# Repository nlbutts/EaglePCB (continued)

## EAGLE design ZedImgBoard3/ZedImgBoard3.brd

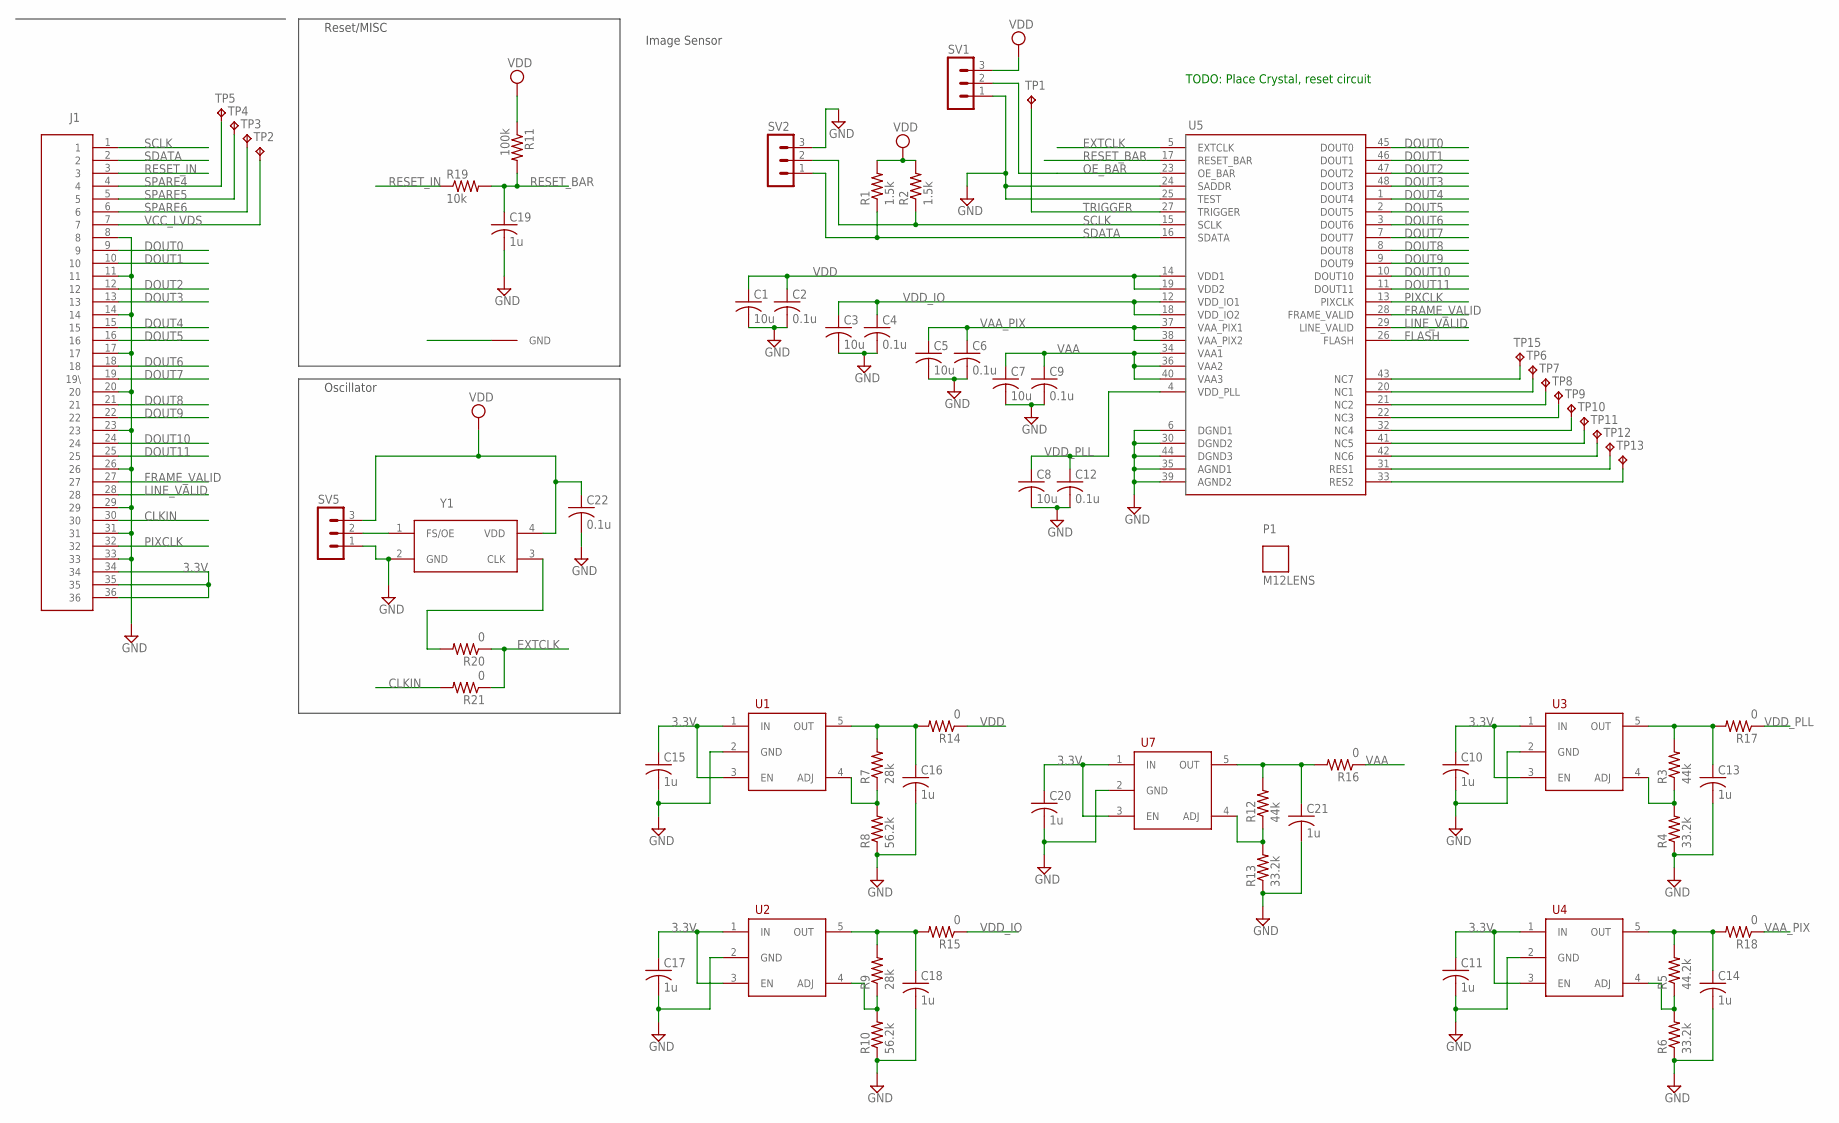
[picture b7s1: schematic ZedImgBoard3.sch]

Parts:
C1, C3, C5, C7, C8: 10u; C0805
C2, C4, C6, C9, C12, C22: 0.1u; C0805
C10, C11, C13, C14, C15, C16, C17, C18, C19, C20, C21: 1u; C0805
J1: MOLEX_54132_3662
P1: M12LENS
R1, R2: 1.5k; M0805
R3, R12: 44k; M0805
R4, R6, R13: 33.2k; M0805
R5: 44.2k; M0805
R7, R9: 28k; M0805
R8, R10: 56.2k; M0805
R11: 100k; M0805
R14, R15, R16, R17, R18, R20, R21: 0; M0805
R19: 10k; M0805
SV1, SV2, SV5: MA03-1
TP1, TP2, TP3, TP4, TP5, TP6, TP7, TP8, TP9, TP10, TP11, TP12, TP13, TP15: TPB1,27; B1,27
U1, U2, U3, U4, U7: TPS73201DB; SOT23-5
U5: AR0331; ILCC48
U$4: GND_LUG; GND_PAD
Y1: SILABS_501AAAXXD; 4-SMD

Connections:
1.8V: R1.2, R2.2
3.3V: C10.1, C11.1, C15.1, C17.1, C20.1, J1.34, J1.35, J1.36, U1.1 (IN), U1.3 (EN), U2.1 (IN), U2.3 (EN), U3.1 (IN), U3.3 (EN), U4.1 (IN), U4.3 (EN), U7.1 (IN), U7.3 (EN)
CLKIN: J1.30, R21.2
DOUT0: J1.9, U5.45 (DOUT0)
DOUT1: J1.10, U5.46 (DOUT1)
DOUT2: J1.12, U5.47 (DOUT2)
DOUT3: J1.13, U5.48 (DOUT3)
DOUT4: J1.15, U5.1 (DOUT4)
DOUT5: J1.16, U5.2 (DOUT5)
DOUT6: J1.18, U5.3 (DOUT6)
DOUT7: J1.19 (19\), U5.7 (DOUT7)
DOUT8: J1.21, U5.8 (DOUT8)
DOUT9: J1.22, U5.9 (DOUT9)
DOUT10: J1.24, U5.10 (DOUT10)
DOUT11: J1.25, U5.11 (DOUT11)
EXTCLK: R20.1, R21.1, U5.5 (EXTCLK)
FLASH: U5.26 (FLASH)
FRAME_VALID: J1.27, U5.28 (FRAME_VALID)
GND: C1.2, C2.2, C3.2, C4.2, C5.2, C6.2, C7.2, C8.2, C9.2, C10.2, C11.2, C12.2, C13.2, C14.2, C15.2, C16.2, C17.2, C18.2, C19.2, C20.2, C21.2, C22.2, J1.8, J1.11, J1.14, J1.17, J1.20, J1.23, J1.26, J1.29, J1.31, J1.33, R4.1, R6.1, R8.1, R10.1, R13.1, SV1.1, SV2.3, SV5.1, U1.2 (GND), U2.2 (GND), U3.2 (GND), U4.2 (GND), U5.6 (DGND1), U5.24 (SADDR), U5.25 (TEST), U5.30 (DGND2), U5.35 (AGND1), U5.39 (AGND2), U5.44 (DGND3), U7.2 (GND), U$4.P$1, Y1.2 (GND)
LINE_VALID: J1.28, U5.29 (LINE_VALID)
unnamed: R7.1, R8.2, U1.4 (ADJ)
unnamed: R9.1, R10.2, U2.4 (ADJ)
unnamed: R12.1, R13.2, U7.4 (ADJ)
unnamed: TP15.TP, U5.43 (NC7)
unnamed: TP6.TP, U5.20 (NC1)
unnamed: TP7.TP, U5.21 (NC2)
unnamed: TP8.TP, U5.22 (NC3)
unnamed: TP9.TP, U5.32 (NC4)
unnamed: TP10.TP, U5.41 (NC5)
unnamed: TP11.TP, U5.42 (NC6)
unnamed: TP12.TP, U5.31 (RES1)
unnamed: TP13.TP, U5.33 (RES2)
unnamed: SV5.2, Y1.1 (FS/OE)
unnamed: R20.2, Y1.3 (CLK)
unnamed: R3.1, R4.2, U3.4 (ADJ)
unnamed: R5.1, R6.2, U4.4 (ADJ)
OE_BAR: SV1.2, U5.23 (OE_BAR)
PIXCLK: J1.32, U5.13 (PIXCLK)
RESET_BAR: C19.1, R11.2, R19.2, U5.17 (RESET_BAR)
RESET_IN: J1.3, R19.1
SCLK: J1.1, R2.1, SV2.2, U5.15 (SCLK)
SDATA: J1.2, R1.1, SV2.1, U5.16 (SDATA)
SPARE4: J1.4, TP5.TP
SPARE5: J1.5, TP4.TP
SPARE6: J1.6, TP3.TP
TRIGGER: TP1.TP, U5.27 (TRIGGER)
VAA: C7.1, C9.1, R16.1, U5.34 (VAA1), U5.36 (VAA2), U5.40 (VAA3)
VAA_H: C21.1, R12.2, R16.2, U7.5 (OUT)
VAA_PIX: C5.1, C6.1, R18.1, U5.37 (VAA_PIX1), U5.38 (VAA_PIX2)
VAA_PIX_H: C14.1, R5.2, R18.2, U4.5 (OUT)
VCC_LVDS: J1.7, TP2.TP
VDD: C1.1, C2.1, C22.1, R11.1, R14.1, SV1.3, SV5.3, U5.14 (VDD1), U5.19 (VDD2), Y1.4 (VDD)
VDD_H: C16.1, R7.2, R14.2, U1.5 (OUT)
VDD_IO: C3.1, C4.1, R15.1, U5.12 (VDD_IO1), U5.18 (VDD_IO2)
VDD_IO_H: C18.1, R9.2, R15.2, U2.5 (OUT)
VDD_PLL: C8.1, C12.1, R17.1, U5.4 (VDD_PLL)
VDD_PLL_H: C13.1, R3.2, R17.2, U3.5 (OUT)

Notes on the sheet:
TODO: Place Crystal, reset circuit
Reset/MISC
Image Sensor
Oscillator

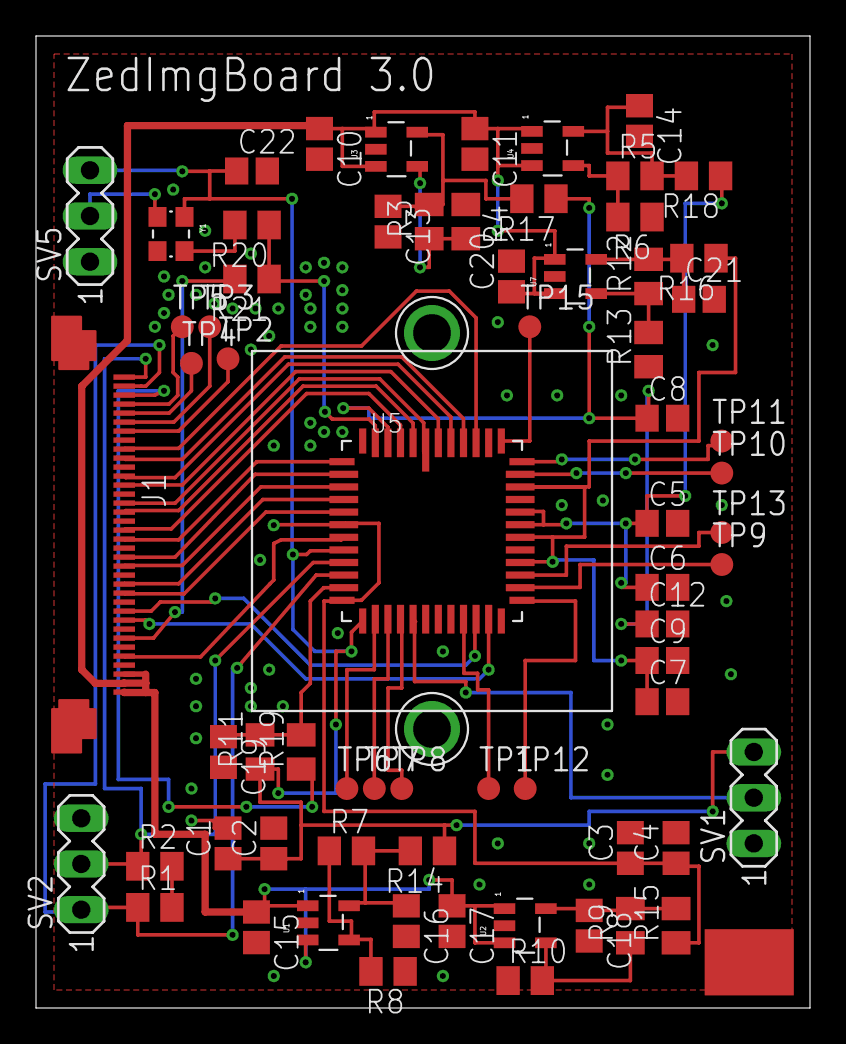
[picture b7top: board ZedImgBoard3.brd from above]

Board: 2 copper layers, 43.0 x 54.0 mm, 70 parts (0 on the bottom side), 56 nets.

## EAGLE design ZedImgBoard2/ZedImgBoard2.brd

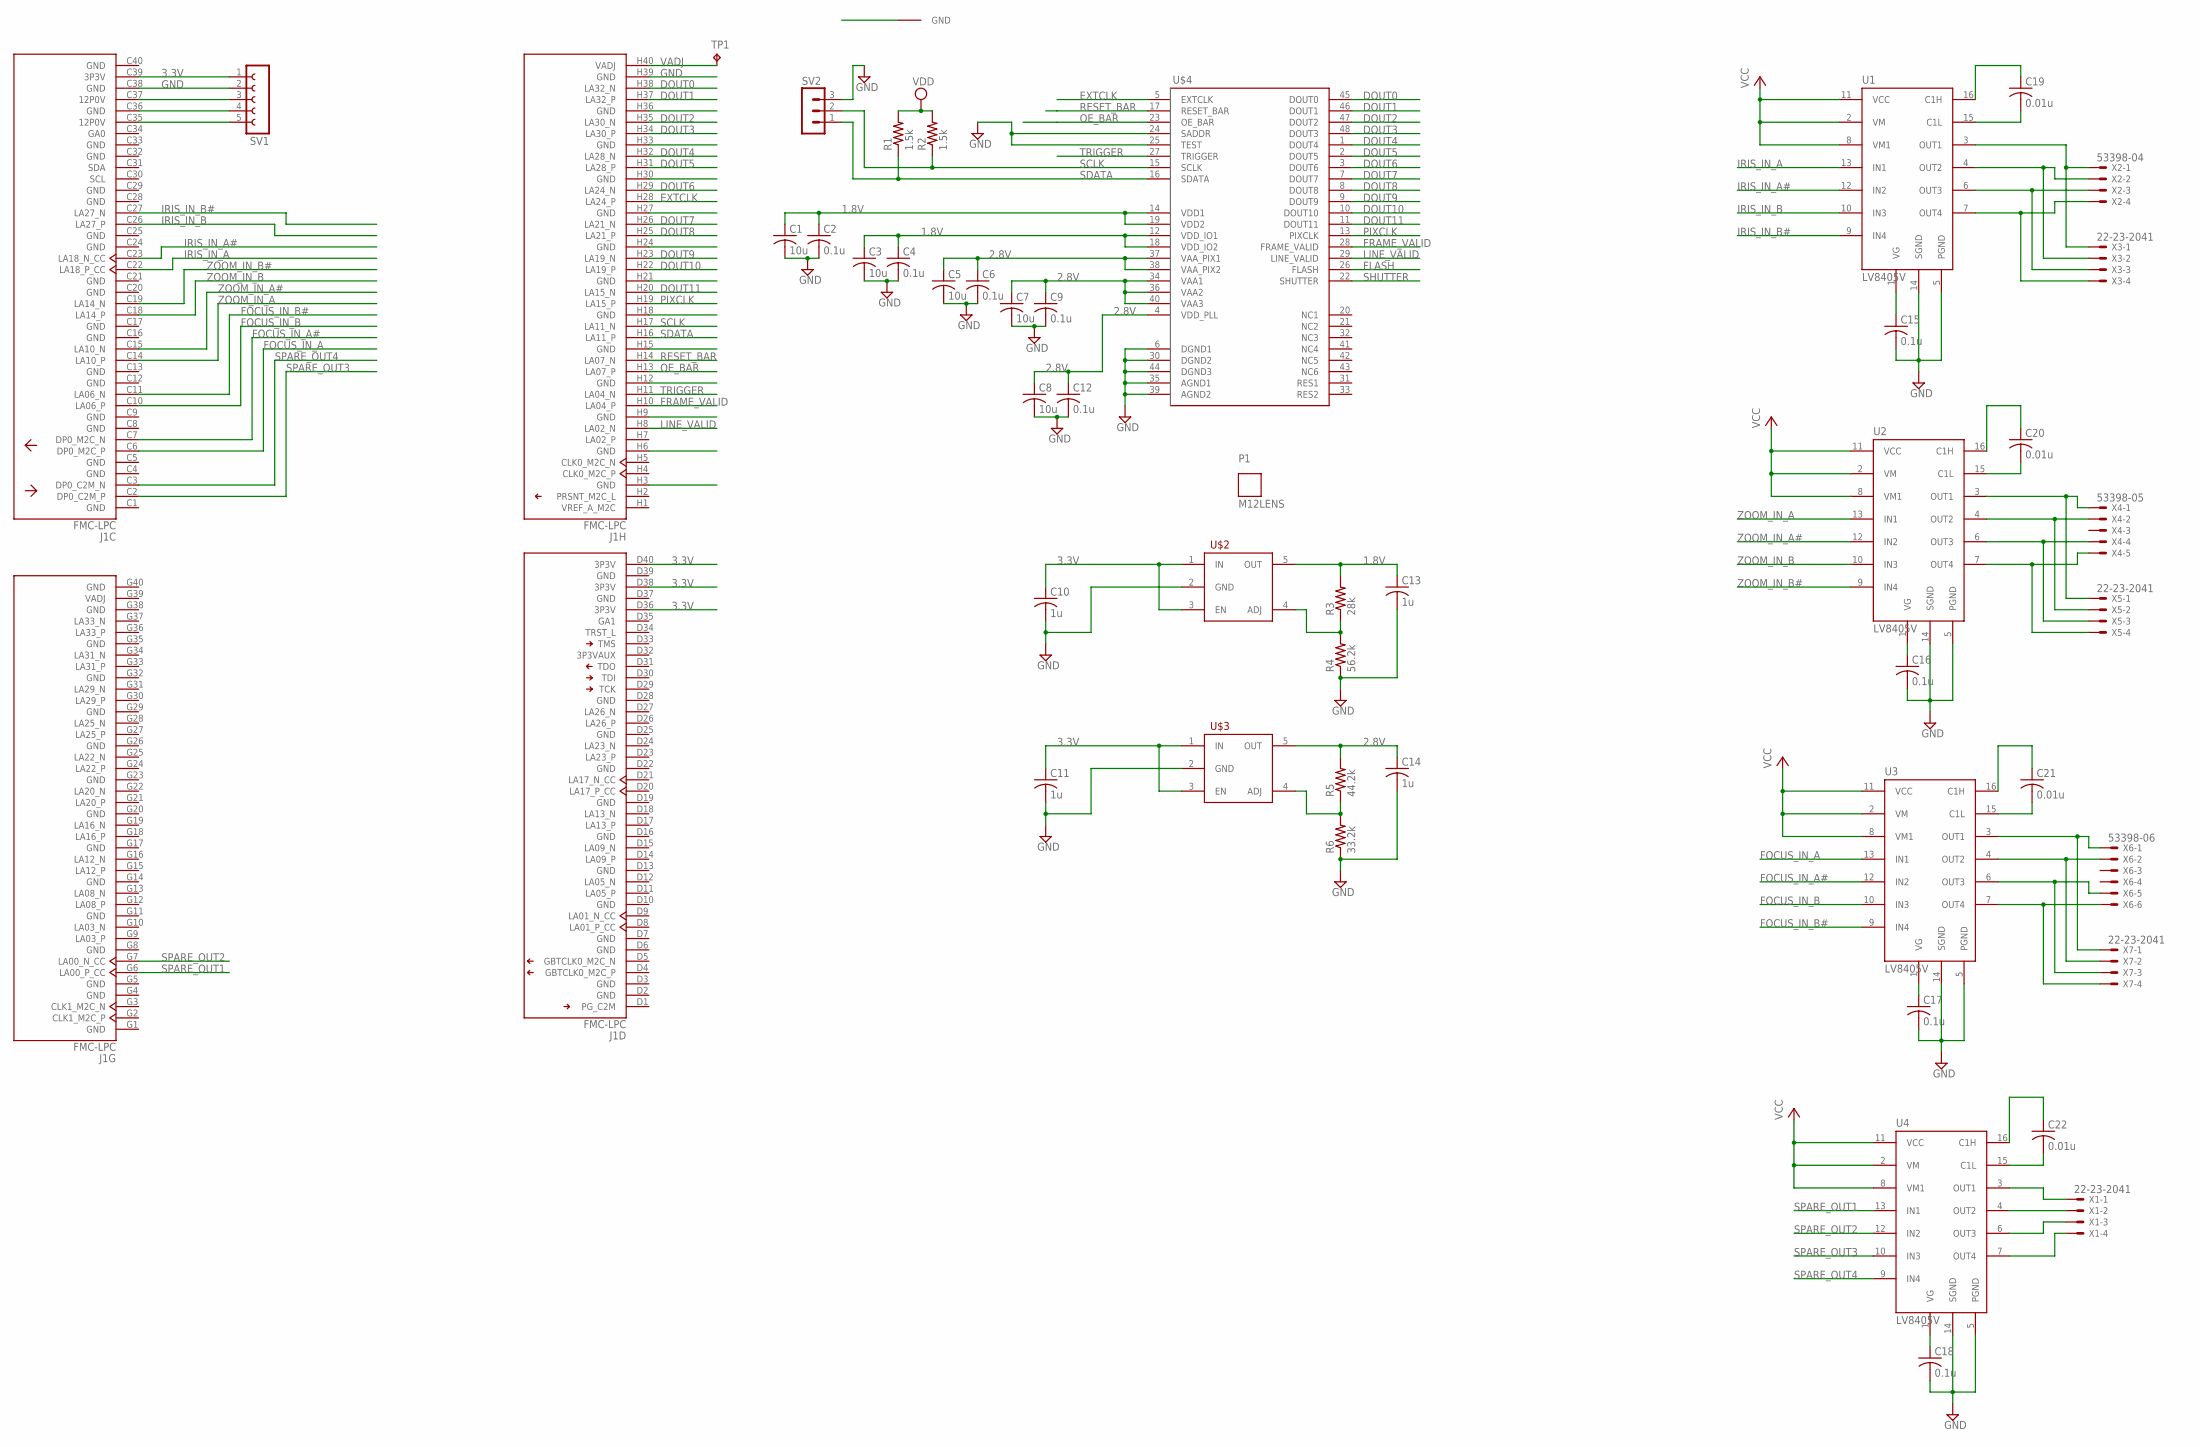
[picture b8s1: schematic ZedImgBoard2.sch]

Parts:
C1, C3, C5, C7, C8: 10u; C0805
C2, C4, C6, C9, C12, C15, C16, C17, C18: 0.1u; C0805
C10, C11, C13, C14: 1u; C0805
C19, C20, C21, C22: 0.01u; C0805
J1: FMC-LPC; FMC-LPC-MALE
P1: M12LENS
R1, R2: 1.5k; M0805
R3: 28k; M0805
R4: 56.2k; M0805
R5: 44.2k; M0805
R6: 33.2k; M0805
SV1: FE05-1
SV2: MA03-1
TP1: TPB1,27; B1,27
U1, U2, U3, U4: LV8405V; SSOP16
U$1: GND_LUG; GND_PAD
U$2, U$3: TPS73201DB; SOT23-5
U$4: AR0331; ILCC48
X1, X3, X5, X7: 22-23-2041
X2: 53398-04
X4: 53398-05
X6: 53398-06

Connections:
1.8V: C1.1, C2.1, C3.1, C4.1, C13.1, R1.2, R2.2, R3.2, U$2.5 (OUT), U$4.12 (VDD_IO1), U$4.14 (VDD1), U$4.18 (VDD_IO2), U$4.19 (VDD2)
2.8V: C5.1, C6.1, C7.1, C8.1, C9.1, C12.1, C14.1, R5.2, U$3.5 (OUT), U$4.4 (VDD_PLL), U$4.34 (VAA1), U$4.36 (VAA2), U$4.37 (VAA_PIX1), U$4.38 (VAA_PIX2), U$4.40 (VAA3)
3.3V: C10.1, C11.1, J1.C39 (3P3V), J1.D36 (3P3V), J1.D38 (3P3V), J1.D40 (3P3V), SV1.1, U1.2 (VM), U1.8 (VM1), U1.11 (VCC), U2.2 (VM), U2.8 (VM1), U2.11 (VCC), U3.2 (VM), U3.8 (VM1), U3.11 (VCC), U4.2 (VM), U4.8 (VM1), U4.11 (VCC), U$2.1 (IN), U$2.3 (EN), U$3.1 (IN), U$3.3 (EN)
DOUT0: J1.H38 (LA32_N), U$4.45 (DOUT0)
DOUT1: J1.H37 (LA32_P), U$4.46 (DOUT1)
DOUT2: J1.H35 (LA30_N), U$4.47 (DOUT2)
DOUT3: J1.H34 (LA30_P), U$4.48 (DOUT3)
DOUT4: J1.H32 (LA28_N), U$4.1 (DOUT4)
DOUT5: J1.H31 (LA28_P), U$4.2 (DOUT5)
DOUT6: J1.H29 (LA24_N), U$4.3 (DOUT6)
DOUT7: J1.H26 (LA21_N), U$4.7 (DOUT7)
DOUT8: J1.H25 (LA21_P), U$4.8 (DOUT8)
DOUT9: J1.H23 (LA19_N), U$4.9 (DOUT9)
DOUT10: J1.H22 (LA19_P), U$4.10 (DOUT10)
DOUT11: J1.H20 (LA15_N), U$4.11 (DOUT11)
EXTCLK: J1.H28 (LA24_P), U$4.5 (EXTCLK)
FLASH: U$4.26 (FLASH)
FOCUS_IN_A: J1.C6 (DP0_M2C_P), U3.13 (IN1)
FOCUS_IN_A#: J1.C7 (DP0_M2C_N), U3.12 (IN2)
FOCUS_IN_B: J1.C10 (LA06_P), U3.10 (IN3)
FOCUS_IN_B#: J1.C11 (LA06_N), U3.9 (IN4)
FRAME_VALID: J1.H10 (LA04_P), U$4.28 (FRAME_VALID)
GND: C1.2, C2.2, C3.2, C4.2, C5.2, C6.2, C7.2, C8.2, C9.2, C10.2, C11.2, C12.2, C13.2, C14.2, C15.2, C16.2, C17.2, C18.2, J1.C38 (GND), J1.H3 (GND), J1.H6 (GND), J1.H9 (GND), J1.H12 (GND), J1.H15 (GND), J1.H18 (GND), J1.H21 (GND), J1.H24 (GND), J1.H27 (GND), J1.H30 (GND), J1.H33 (GND), J1.H36 (GND), J1.H39 (GND), R4.1, R6.1, SV1.2, SV2.3, U1.5 (PGND), U1.14 (SGND), U2.5 (PGND), U2.14 (SGND), U3.5 (PGND), U3.14 (SGND), U4.5 (PGND), U4.14 (SGND), U$1.P$1, U$2.2 (GND), U$3.2 (GND), U$4.6 (DGND1), U$4.24 (SADDR), U$4.25 (TEST), U$4.30 (DGND2), U$4.35 (AGND1), U$4.39 (AGND2), U$4.44 (DGND3)
IRIS_IN_A: J1.C22 (LA18_P_CC), U1.13 (IN1)
IRIS_IN_A#: J1.C23 (LA18_N_CC), U1.12 (IN2)
IRIS_IN_B: J1.C26 (LA27_P), U1.10 (IN3)
IRIS_IN_B#: J1.C27 (LA27_N), U1.9 (IN4)
LINE_VALID: J1.H8 (LA02_N), U$4.29 (LINE_VALID)
unnamed: U1.3 (OUT1), X2.1, X3.1
unnamed: U1.4 (OUT2), X2.2, X3.2
unnamed: U1.6 (OUT3), X2.3, X3.3
unnamed: U2.3 (OUT1), X4.1, X5.1
unnamed: U2.4 (OUT2), X4.2, X5.2
unnamed: U2.6 (OUT3), X4.4, X5.3
unnamed: U2.7 (OUT4), X4.5, X5.4
unnamed: U3.3 (OUT1), X6.1, X7.1
unnamed: U3.4 (OUT2), X6.2, X7.2
unnamed: U3.6 (OUT3), X6.5, X7.3
unnamed: U3.7 (OUT4), X6.6, X7.4
unnamed: C19.2, U1.15 (C1L)
unnamed: C19.1, U1.16 (C1H)
unnamed: C15.1, U1.1 (VG)
unnamed: C20.2, U2.15 (C1L)
unnamed: C20.1, U2.16 (C1H)
unnamed: C16.1, U2.1 (VG)
unnamed: C21.2, U3.15 (C1L)
unnamed: C21.1, U3.16 (C1H)
unnamed: C17.1, U3.1 (VG)
unnamed: U1.7 (OUT4), X2.4, X3.4
unnamed: C22.2, U4.15 (C1L)
unnamed: C22.1, U4.16 (C1H)
unnamed: R3.1, R4.2, U$2.4 (ADJ)
unnamed: J1.C37 (12P0V), SV1.3
unnamed: J1.C36 (GND), SV1.4
unnamed: R5.1, R6.2, U$3.4 (ADJ)
unnamed: J1.C35 (12P0V), SV1.5
unnamed: C18.1, U4.1 (VG)
unnamed: U4.3 (OUT1), X1.1
unnamed: U4.4 (OUT2), X1.2
unnamed: U4.6 (OUT3), X1.3
unnamed: U4.7 (OUT4), X1.4
OE_BAR: J1.H13 (LA07_P), U$4.23 (OE_BAR)
PIXCLK: J1.H19 (LA15_P), U$4.13 (PIXCLK)
RESET_BAR: J1.H14 (LA07_N), U$4.17 (RESET_BAR)
SCLK: J1.H17 (LA11_N), R2.1, SV2.2, U$4.15 (SCLK)
SDATA: J1.H16 (LA11_P), R1.1, SV2.1, U$4.16 (SDATA)
SHUTTER: U$4.22 (SHUTTER)
SPARE_OUT1: J1.G6 (LA00_P_CC), U4.13 (IN1)
SPARE_OUT2: J1.G7 (LA00_N_CC), U4.12 (IN2)
SPARE_OUT3: J1.C2 (DP0_C2M_P), U4.10 (IN3)
SPARE_OUT4: J1.C3 (DP0_C2M_N), U4.9 (IN4)
TRIGGER: J1.H11 (LA04_N), U$4.27 (TRIGGER)
VADJ: J1.H40 (VADJ), TP1.TP
ZOOM_IN_A: J1.C14 (LA10_P), U2.13 (IN1)
ZOOM_IN_A#: J1.C15 (LA10_N), U2.12 (IN2)
ZOOM_IN_B: J1.C18 (LA14_P), U2.10 (IN3)
ZOOM_IN_B#: J1.C19 (LA14_N), U2.9 (IN4)

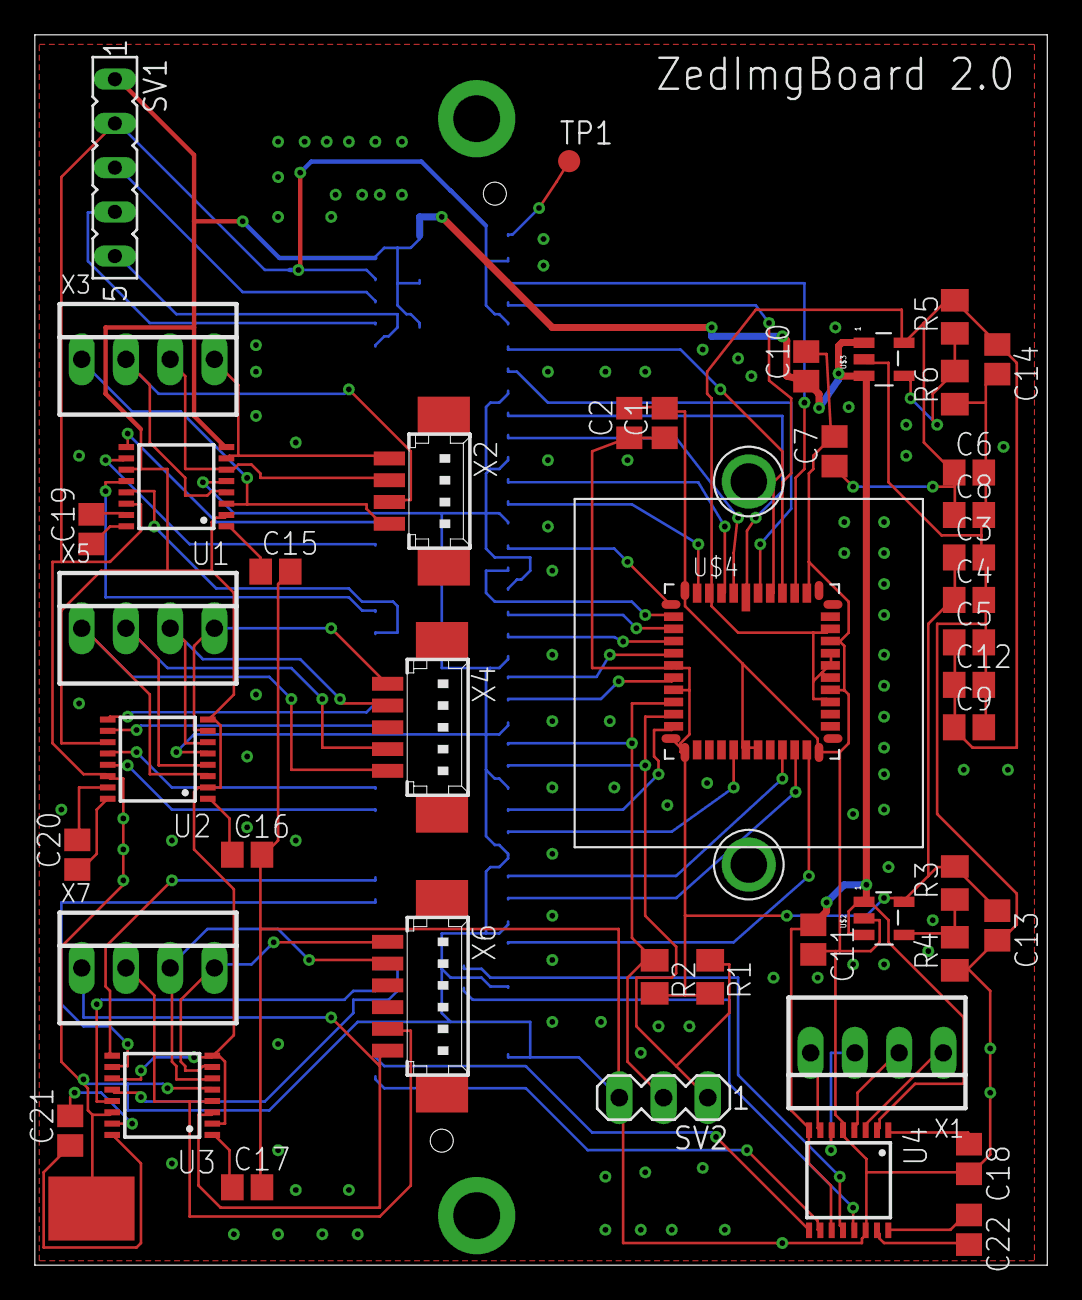
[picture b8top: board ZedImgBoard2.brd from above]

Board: 2 copper layers, 58.1 x 70.7 mm, 48 parts (0 on the bottom side), 75 nets.

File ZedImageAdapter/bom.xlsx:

| Partl | ist exporte | d from C: | /projects/Eagle | /ZedImageA | dapter/ze | d_image_adapter.sch at 3/15/2014 2:13:05 PM
Digikey Part # | Part | Value | Device | Package | Descriptio | n | MF MPN OC_FARNELL OC_NEWARK TP_SIGNAL_NAME
1276-1096-1-ND | C1 | 10u | C-USC0805 | C0805 | CAPACITOR, | American | symbol
1276-1099-1-ND | C2 | 0.1u | C-USC0805 | C0805 | CAPACITOR, | American | symbol
1276-1096-1-ND | C3 | 10u | C-USC0805 | C0805 | CAPACITOR, | American | symbol
1276-1099-1-ND | C4 | 0.1u | C-USC0805 | C0805 | CAPACITOR, | American | symbol
1276-1096-1-ND | C5 | 10u | C-USC0805 | C0805 | CAPACITOR, | American | symbol
1276-1099-1-ND | C6 | 0.1u | C-USC0805 | C0805 | CAPACITOR, | American | symbol
1276-1096-1-ND | C7 | 10u | C-USC0805 | C0805 | CAPACITOR, | American | symbol
1276-1096-1-ND | C8 | 10u | C-USC0805 | C0805 | CAPACITOR, | American | symbol
1276-1099-1-ND | C9 | 0.1u | C-USC0805 | C0805 | CAPACITOR, | American | symbol
1276-1029-1-ND | C10 | 1u | C-USC0805 | C0805 | CAPACITOR, | American | symbol
1276-1029-1-ND | C11 | 1u | C-USC0805 | C0805 | CAPACITOR, | American | symbol
1276-1099-1-ND | C12 | 0.1u | C-USC0805 | C0805 | CAPACITOR, | American | symbol
1276-1029-1-ND | C13 | 1u | C-USC0805 | C0805 | CAPACITOR, | American | symbol
1276-1029-1-ND | C14 | 1u | C-USC0805 | C0805 | CAPACITOR, | American | symbol
1276-1099-1-ND | C15 | 0.1u | C-USC0805 | C0805 | CAPACITOR, | American | symbol
1276-1099-1-ND | C16 | 0.1u | C-USC0805 | C0805 | CAPACITOR, | American | symbol
1276-1099-1-ND | C17 | 0.1u | C-USC0805 | C0805 | CAPACITOR, | American | symbol
1276-1015-1-ND | C18 | 0.01u | C-USC0805 | C0805 | CAPACITOR, | American | symbol
1276-1015-1-ND | C19 | 0.01u | C-USC0805 | C0805 | CAPACITOR, | American | symbol
1276-1015-1-ND | C20 | 0.01u | C-USC0805 | C0805 | CAPACITOR, | American | symbol
1276-1015-1-ND | C21 | 0.01u | C-USC0805 | C0805 | CAPACITOR, | American | symbol
1276-1099-1-ND | C22 | 0.1u | C-USC0805 | C0805 | CAPACITOR, | American | symbol
 | J1 | FMC-LPC | FMC-LPC | FMC-LPC-MALE | FMC-LPC |  | unknown
 | P1 | M12LENS | M12LENS | M12LENS
P1.50KCCT-ND | R1 | 1.5k | R-US_M080 | 5 M0805 | RESISTOR, | American | symbol
P1.50KCCT-ND | R2 | 1.5k | R-US_M080 | 5 M0805 | RESISTOR, | American | symbol
P28.0KCCT-ND | R3 | 28k | R-US_M080 | 5 M0805 | RESISTOR, | American | symbol
P56.2KHCT-ND | R4 | 56.2k | R-US_M080 | 5 M0805 | RESISTOR, | American | symbol
P44.2KHCT-ND | R5 | 44.2k | R-US_M080 | 5 M0805 | RESISTOR, | American | symbol
P33.2KCCT-ND | R6 | 33.2k | R-US_M080 | 5 M0805 | RESISTOR, | American | symbol
609-3287-ND | SV1 |  | FE05-1 | FE05-1 | FEMALE HEA | DER | unknown unknown
609-3287-ND | SV2 |  | MA03-1 | MA03-1 | PIN HEADER |  | unknown unknown
 | TP1 | TPB1,27 | TPB1,27 | B1,27 | Test pad
296-32554-1-ND | U$1 | TPS73201DB | TPS73201D | B SOT23-5
296-32554-1-ND | U$2 | TPS73201DB | TPS73201D | B SOT23-5
 | U$3 |  | AR0331 | ILCC48
5016KCT-ND | U$4 | GND_LUG | GND_LUG | GND_PAD
869-1283-1-ND | U1 | LV8405V | LV8405V | SSOP16
869-1283-1-ND | U2 | LV8405V | LV8405V | SSOP16
869-1283-1-ND | U3 | LV8405V | LV8405V | SSOP16
869-1283-1-ND | U4 | LV8405V | LV8405V | SSOP16
WM7608CT-ND | X1 | 53398-04 | 53398-04 | 53398-04 | CONNECTOR |  | 1125367 unknown
609-3287-ND | X2 | 22-23-2041 | 22-23-204 | 1 22-23-2041 | .100" (2.5 | 4mm) Cent | er Header - 4 Pin MOLEX 22-23-2041 1462920 38C0355
WM7609CT-ND | X3 | 53398-05 | 53398-05 | 53398-05 | CONNECTOR |  | 1125354 unknown
609-3287-ND | X4 | 22-23-2041 | 22-23-204 | 1 22-23-2041 | .100" (2.5 | 4mm) Cent | er Header - 4 Pin MOLEX 22-23-2041 1462920 38C0355
WM7610CT-ND | X5 | 53398-06 | 53398-06 | 53398-06 | CONNECTOR |  | 1125368 unknown
609-3287-ND | X6 | 22-23-2041 | 22-23-204 | 1 22-23-2041 | .100" (2.5 | 4mm) Cent | er Header - 4 Pin MOLEX 22-23-2041 1462920 38C0355
609-3287-ND | X9 | 22-23-2041 | 22-23-204 | 1 22-23-2041 | .100" (2.5 | 4mm) Cent | er Header - 4 Pin MOLEX 22-23-2041 1462920 38C0355

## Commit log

2016-03-16 Migrated Eagle PCB projects from Hg to GIT.
2016-03-16 Added Jay's ECU adapter.
2016-03-18 Switched to a smaller board, completed the routing.
2016-03-18 Added Ver string.
2016-03-18 Increased trace thickness.
2016-06-06 Added a design doc.
2016-06-10 Removed the processor and simplified the POVDisplayBase
2016-06-10 Added the POVDisplayRotate project.
2016-06-10 Minor updates to the silkscreen.
2016-06-16 Added the POVDisplayRotate schematic and board design.
2016-06-19 Update the POVDisplayRotate.
2016-08-02 Not sure what I updated.
2016-08-02 Added Jay's car adapter info.
2016-08-02 Started to add the PSoC BLE board
2016-08-03 Added Abercrombie blockage monitor.
2016-08-05 Added the Abercrombie board.
2016-08-05 Finished the schematic and placement. Starting routing for Abercrombie.
2016-08-05 Fully routed Abercrombie design
2016-08-05 Minor update to the BLE connector
2016-08-05 Some of the values got moved to the top layer. This would have been very bad.
2016-08-05 Made some change, not sure what I did.
2016-08-08 Added digikey part numbers for the various components.
2016-08-14 Updated the POVDisplayRotate
2016-08-14 Added datasheets
2016-08-14 Placed most of the components for the POVRotate. Working on PCB.
2016-08-15 Working on the routing of the POVRotate display.
2016-08-15 More routing.
2016-08-15 Updates to library and descriptions.
2016-08-17 Updated the Abercrombie issues.
2016-08-21 Updated to fix issues with the layout.
2016-08-22 Completed the V2 of the Abercrombie sprayer.
2016-08-25 Added additional datasheets and digikey part numbers.
2016-08-25 Completed the routing of the POV Rotate board
2016-08-25 Moved EEP to get more room
2016-08-25 Updated Abercrombie issue list
2016-08-28 Updated the POVBase to use a PSoC, it is about the same price as a 555 and more flexible.
2016-08-29 Order Oshpark boards for POV Rotate and POV Base
2016-09-08 Updated Abercrombie values.
2016-09-13 Added the AbercrombieLaser board
2016-09-13 Cleaned up the datasheet directory for the Abercrombie LED sensor.
2016-09-13 Autorouted the AbercrombieLaser spray monitor
2016-09-14 Routed the Abercrombie Laser project.
2016-09-14 Finializing the design.
2016-09-14 Updated the library and POVDisplay board with part numbers.
2016-09-20 Starting to change the Abercrombie blockage 2 design.
2016-09-20 Added datasheets.
2016-09-21 Updated some issues with the Abercrombie Gen4 spray system. Completely re-routed the design.
2016-09-21 Minor updates to the layout.
2016-09-21 Order V2 of the Gen4 spray pattern monitor.
2016-09-26 Added a readme indicated the Abercrombie projects have been moved.
2016-11-09 Added the POVRotateBasic
